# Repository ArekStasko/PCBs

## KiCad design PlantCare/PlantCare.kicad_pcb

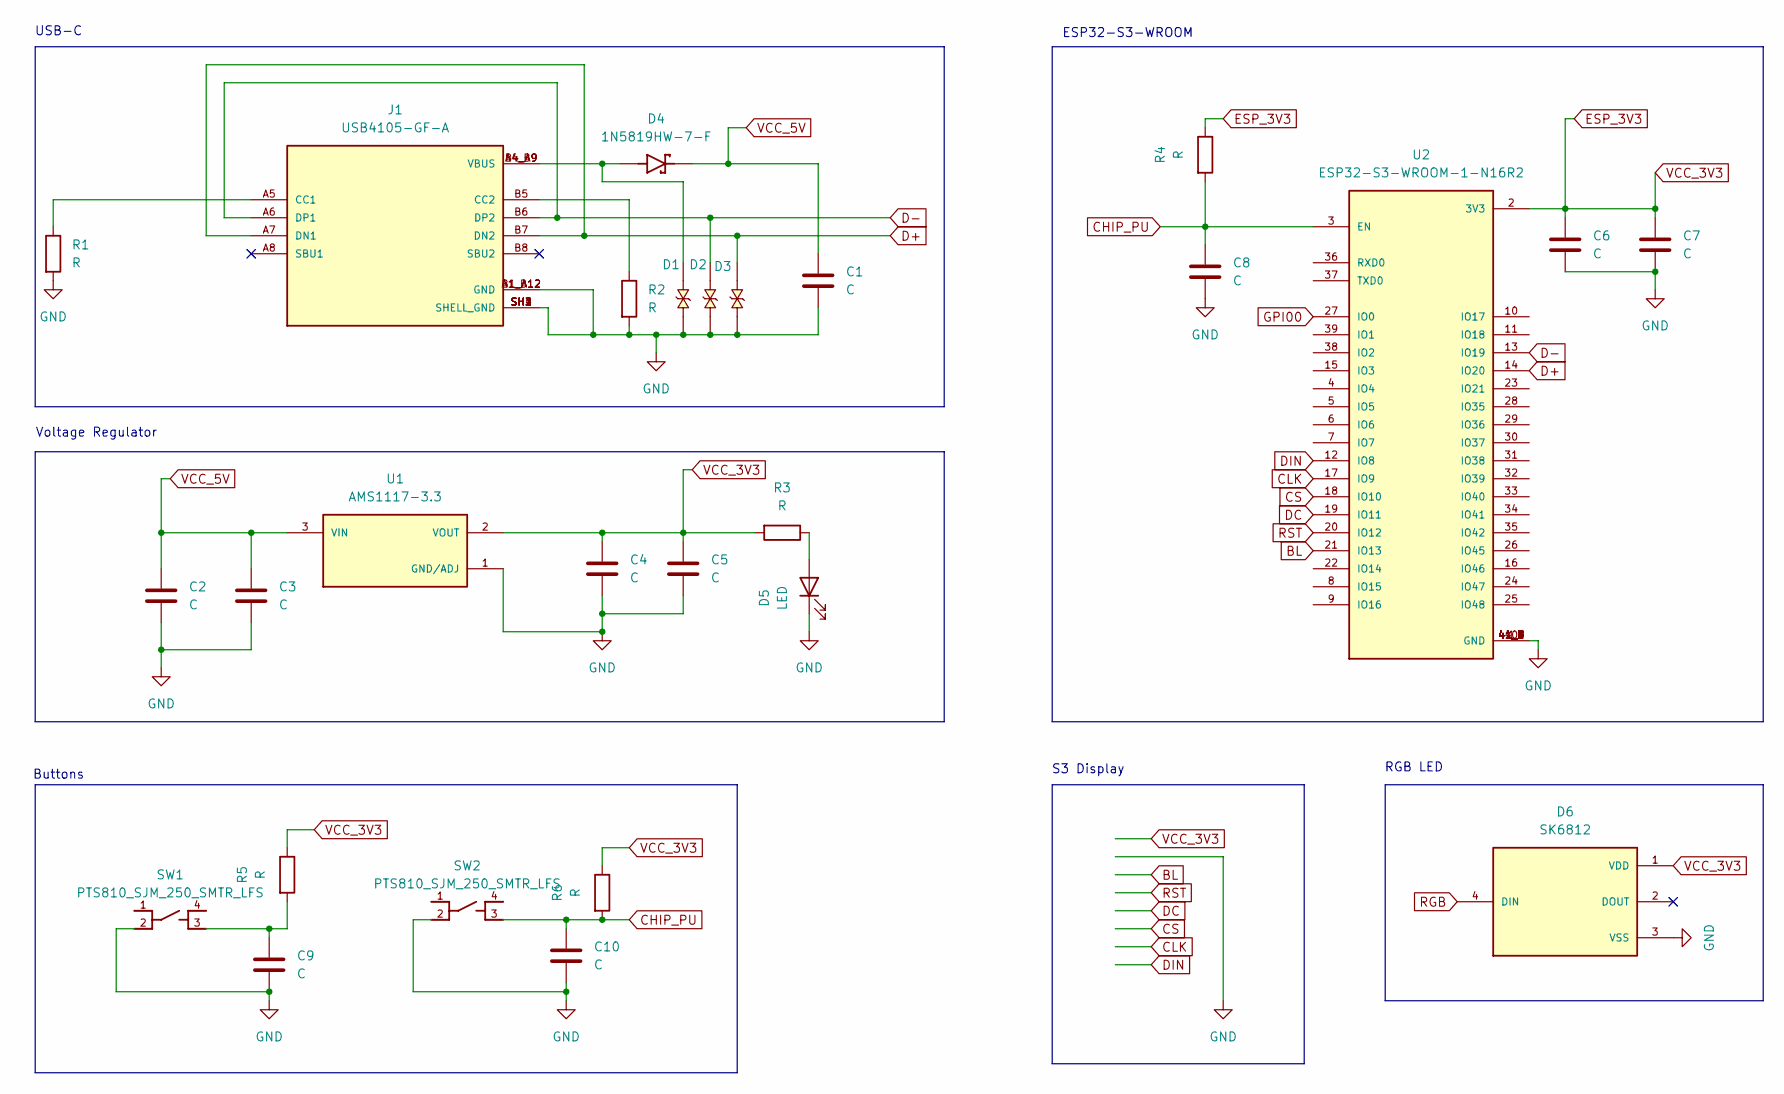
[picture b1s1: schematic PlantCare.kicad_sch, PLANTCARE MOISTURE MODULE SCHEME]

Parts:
C1, C2, C3, C4, C5, C6, C7, C8, C9, C10: C; CP_EIA-1608-08_AVX-J
D1, D2, D3: TVS_LESD5D5.0CT1G; PARTREV O
D4: 1N5819HW-7-F; SOD3715X145N; PARTREV 18-2
D5: LED; D_0805_2012Metric
D6: SK6812; LED_SK6812; PARTREV 03
J1: USB4105-GF-A; GCT_USB4105-GF-A; PARTREV B4
R1, R2, R3, R4, R5, R6: R; R_0201_0603Metric
SW1, SW2: PTS810_SJM_250_SMTR_LFS; SW_PTS810_SJM_250_SMTR_LFS
U1: AMS1117-3.3; SOT229P700X180-4N; PARTREV N/A
U2: ESP32-S3-WROOM-1-N16R2; XCVR_ESP32-S3-WROOM-1-N16R2; PARTREV v1.0

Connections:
BL: U2.21 (IO13)
CHIP_PU: C8.1, C10.1, R4.2, R6.2, SW2.3, U2.3 (EN)
CLK: U2.17 (IO9)
CS: U2.18 (IO10)
D+: D3.1, J1.A7 (DN1), J1.B7 (DN2), U2.14 (IO20)
D-: D2.1, J1.A6 (DP1), J1.B6 (DP2), U2.13 (IO19)
DC: U2.19 (IO11)
DIN: U2.12 (IO8)
ESP_3V3: C4.1, C5.1, C6.1, C7.1, D6.1 (VDD), R3.2, R4.1, R5.1, R6.1, U1.2 (VOUT), U2.2 (3V3)
GND: C1.2, C2.2, C3.2, C4.2, C5.2, C6.2, C7.2, C8.2, C9.2, C10.2, D1.2, D2.2, D3.2, D5.1 (K), D6.3 (VSS), J1.A1_B12 (GND), J1.B1_A12 (GND), J1.SH1 (SHELL_GND), J1.SH2 (SHELL_GND), J1.SH3 (SHELL_GND), J1.SH4 (SHELL_GND), R1.2, R2.2, SW1.2, SW2.2, U1.1 (GND/ADJ), U2.1 (GND), U2.40 (GND), U2.41_1 (GND), U2.41_2 (GND), U2.41_3 (GND), U2.41_4 (GND), U2.41_5 (GND), U2.41_6 (GND), U2.41_7 (GND), U2.41_8 (GND), U2.41_9 (GND)
GPI00: U2.27 (IO0)
unnamed: C9.1, R5.2, SW1.3
unnamed: D1.1, D4.A, J1.A4_B9 (VBUS), J1.B4_A9 (VBUS)
unnamed: D5.2 (A), R3.1
unnamed: J1.A5 (CC1), R1.1
unnamed: J1.B5 (CC2), R2.1
RGB: D6.4 (DIN)
RST: U2.20 (IO12)
VCC_5V: C1.1, C2.1, C3.1, D4.C, U1.3 (VIN)

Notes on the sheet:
ESP32-S3-WROOM
S3 Display
Voltage Regulator
Buttons
RGB LED
USB-C

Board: 2 copper layers, 27 parts (0 on the bottom side), 11 nets, no tracks yet.

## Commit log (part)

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2024-09-04 Add plantcare pcb
2024-10-01 Add voltage regulator
2024-10-01 Add rgb led
2024-10-02 Add esp32-s3-1-n16r2 scheme
2024-10-03 Add complete schemes
2024-10-05 Link footprints
2024-10-06 Add components
2024-10-07 Clear pcb
2024-10-08 Fix pc
2024-10-10 Clean scheme
2024-10-10 Add power supply scheme
2024-10-10 Add components specifications
2024-10-11 Update scheme
2024-10-13 Add micro usb scheme
2024-10-15 Add esp32 module scheme
2024-10-19 Prepare schematic
2024-10-19 Switch to easyEDA
2024-10-20 Add neccessary parts
2024-10-20 Add parts list with links
2024-10-21 Segregate components
2024-10-22 Add btn to en connector
2024-10-24 Start connecting uart
2024-10-25 Add uart grounding
2024-10-26 Add vbus
2024-10-27 Add led and uart
2024-10-30 Add pin headers
2024-10-31 Done with schematic
2024-10-31 Add pcb starter
2024-11-02 Add base components layout
2025-02-13 Add layout
2025-02-15 Start again
2025-02-16 Add esp32 module schema
2025-02-17 Add usb schema
2025-02-18 Add full usb schema
2025-02-19 Add full uart scheme
2025-02-19 Add connectors and buttons
2025-02-19 Fix nets
2025-02-20 First try
2025-02-21 Add routes
2025-02-22 Start USB component routing
2025-02-24 Add uart
2025-02-25 Add buttons
2025-02-27 Add usb and uart
2025-08-19 Luppiter Controller project
2025-08-20 BMP Module
2025-08-21 TPS Module
2025-08-22 Add transistor
2025-09-06 Plantcare module v4
2025-09-07 Switch bom
2025-09-09 PLantcare module pins for conductor
2025-09-10 Plantcare module sheet
2025-09-11 Revert wrong changes
2025-09-12 Correct routes
2025-09-15 finished pcb
2025-10-08 esp32-devkitc project
2025-11-20 pcb repo sheet
2025-11-20 start pcb
2025-11-21 First version of pcb
2025-11-24 cleanup
2025-11-25 Clear scheet
2025-11-25 Add nice and clear project
2025-11-26 pcb leds position
2025-11-26 Done placing
2025-11-26 gnd connecting
2025-11-28 routes
2025-11-29 Fix routing
2025-11-29 Led routing
2025-11-30 Final routing
2026-03-10 Battery controller parts
2026-03-11 schema
